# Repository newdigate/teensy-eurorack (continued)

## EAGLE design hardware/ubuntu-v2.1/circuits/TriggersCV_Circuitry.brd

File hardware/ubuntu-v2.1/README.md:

# ubuntu instrument v2.1
## [circuits](circuits)
## bom
 * teensy 3.6 board
 * blackaddr teensy guitaar audio pro shield

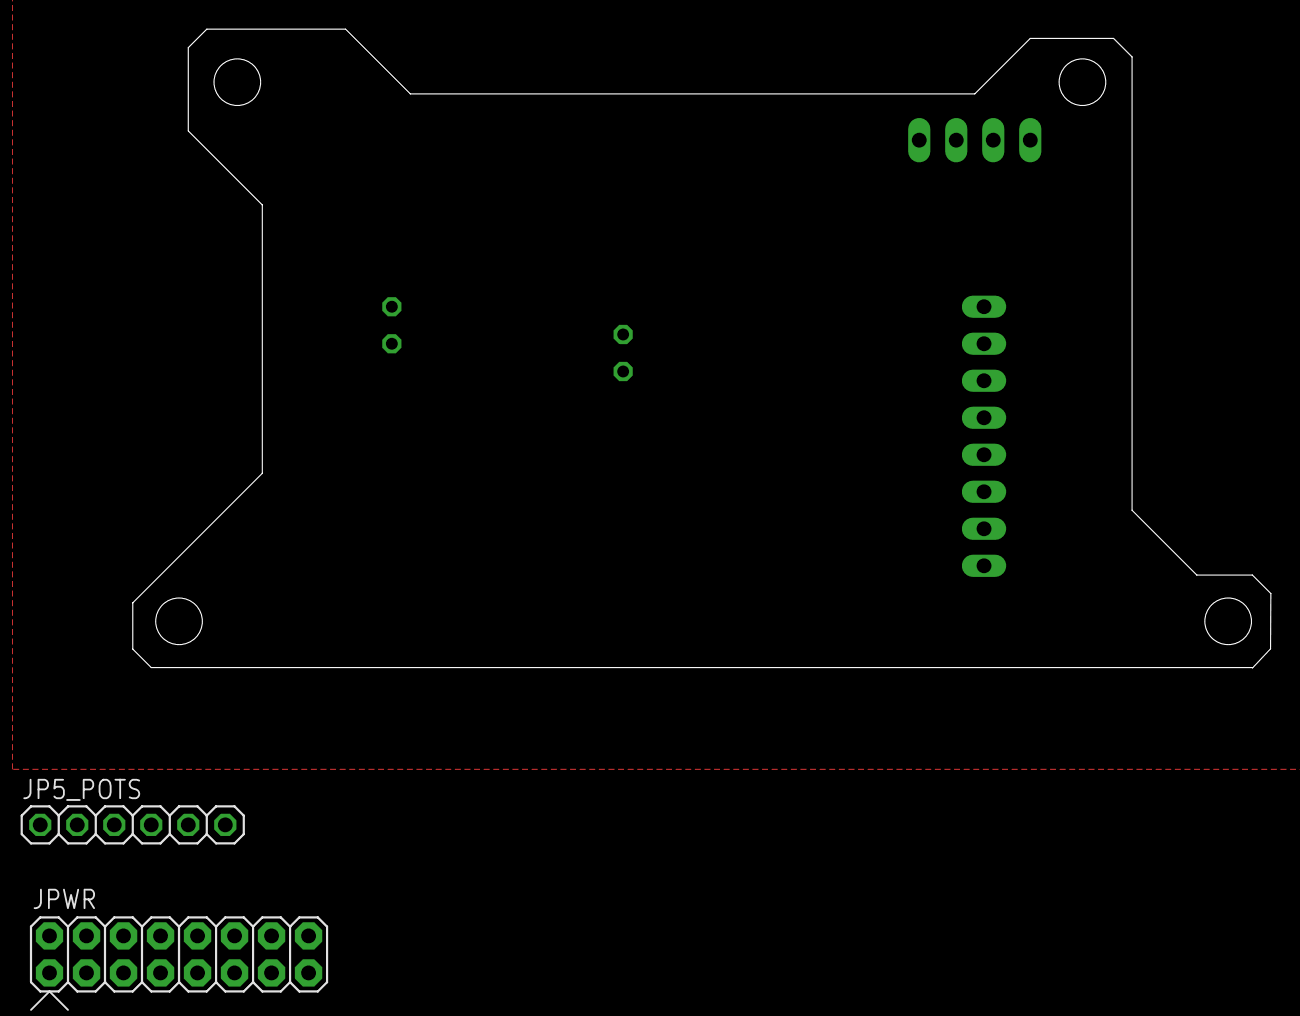
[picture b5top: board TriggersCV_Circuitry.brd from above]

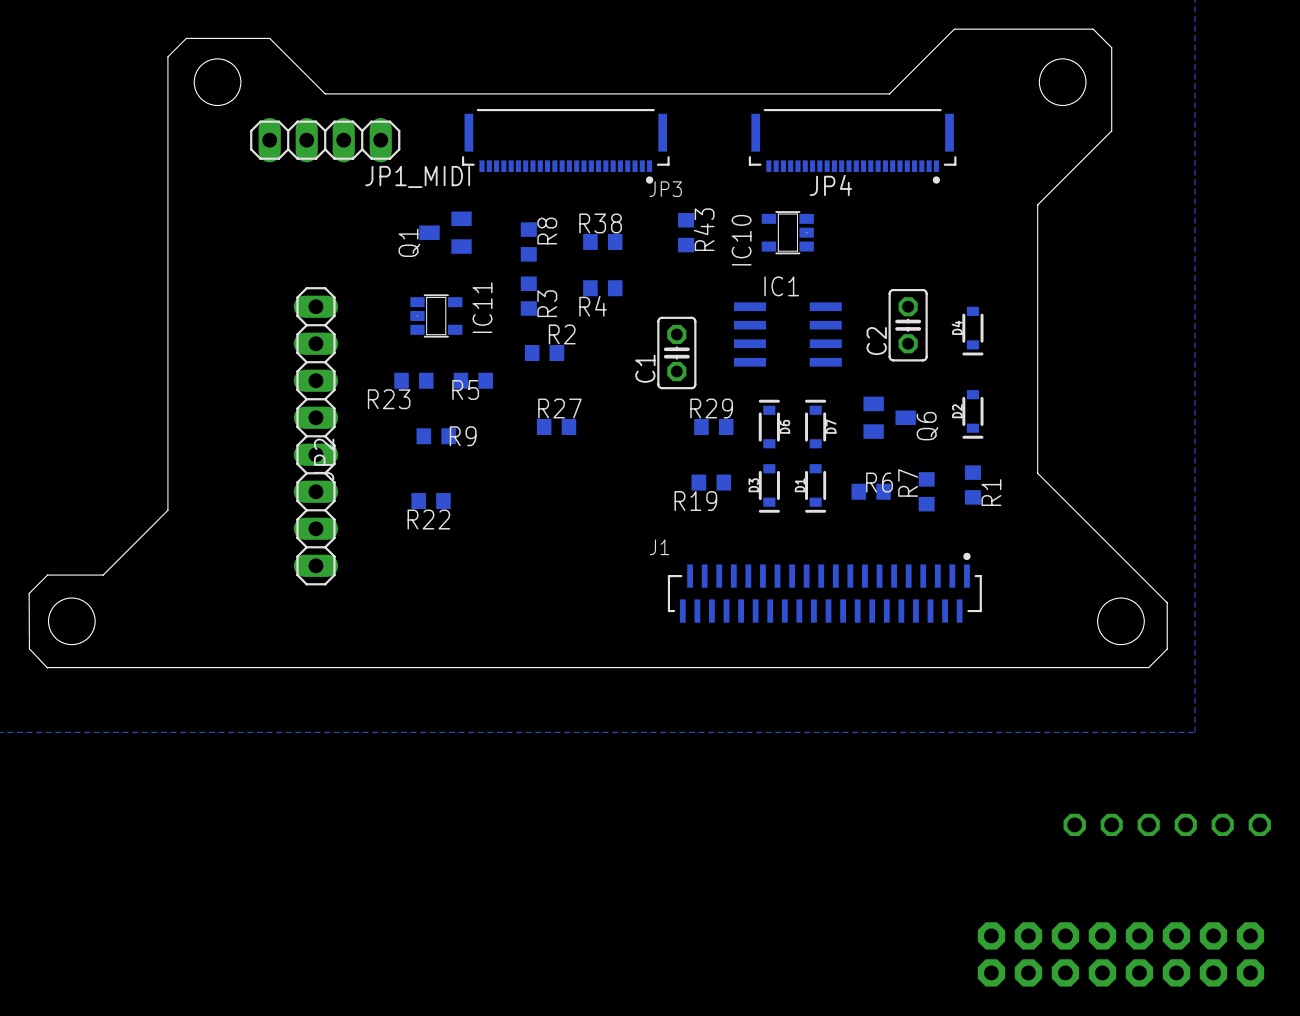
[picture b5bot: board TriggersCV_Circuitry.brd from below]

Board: 2 copper layers, 78.1 x 43.8 mm, 36 parts (34 on the bottom side), 49 nets, no tracks yet.

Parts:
C1, C2: 47p; C025-025X050
D1, D2, D3, D4, D6, D7: 250mA/100V; SPARKFUN-DISCRETESEMI_SOD-323
IC1: TL072D; SO08
IC10, IC11: 74AHCT1G125DBV; SOT23-5
J1: MOLEX_78127-1408MOLEX_78127-1408_0_0; MOLEX_78127-1408_0
JP1_MIDI: 1X04
JP2: 1X08
JP3, JP4: MOLEX_51281-2494MOLEX_51281-2494_0_0; MOLEX_51281-2494_0
JP5_POTS: PINHD-1X6; 1X06
JPWR: POWER; POWER_16
Q1, Q6: MMBT3904; SOT23-BEC
R1, R4, R7, R19: 1K; R0603
R2, R3, R5, R6: 100K; R0603
R8, R29: 100k; R0603
R9, R27: 10k; R0603
R22, R23: 47k; R0603
R38, R43: 1.0k; R0603

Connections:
+3V3: R9.2, R27.2
CV_IN_1: JP3.8, JP3.9
CV_IN_2: D1.A, D2.C, D3.A, D4.C, JP3.7, R1.1, R19.1
CV_OUT_1: JP3.10, JP3.11, R3.1, R4.1
CV_OUT_2: JP3.6, R6.1, R7.1
GND: D2.A, D4.A, D6.A, D7.A, IC1.4, IC10.1, IC10.3, IC11.1, IC11.3, J1.40, JP2.1, JP3.19, JP3.20, JP3.21, JP3.22, JP3.23, JP3.24, JP3.MP1, JP3.MP2, JP4.1, JP4.14, JP5_POTS.3, JP5_POTS.6, JPWR.3, JPWR.4, JPWR.5, JPWR.6, JPWR.7, JPWR.8, Q1.E, Q6.E, R22.1
MIDI_RX_PIN4: JP1_MIDI.1, JP3.12, JP3.13
MIDI_RX_PIN5: JP1_MIDI.2, JP3.14
MIDI_TX_PIN4: JP1_MIDI.3, JP3.15
MIDI_TX_PIN5: JP1_MIDI.4, JP3.16, JP3.17
unnamed: C1.1, IC1.2, R2.1, R3.2
unnamed: C2.1, IC1.6, R5.1, R6.2
unnamed: C1.2, IC1.1, R4.2
unnamed: C2.2, IC1.7, R7.2
unnamed: D7.C, Q1.B, R8.2
unnamed: IC10.4, R38.2
unnamed: IC11.4, R43.2
unnamed: D6.C, Q6.B, R29.2
SPI0_MOSI: J1.34, JP2.4
SPI0_SCLK: J1.37, JP2.3
T2_GATE_IN_A: J1.3, Q6.C, R27.1
T3_GATE_IN_B: J1.4, Q1.C, R9.1
T4_GATE_OUT_A: IC10.2, J1.5
T10_GATE_OUT_B: IC11.2, J1.6
T16_ENC1_A: J1.7, JP4.2
T24_ENC1_B: J1.8, JP4.3
T25_ENC1_SW: J1.9, JP4.4
T26_ENC2_A: J1.10, JP4.5
T27_ENC2_B: J1.11, JP4.6
T28_ENC2_SW: J1.12, JP4.7
T29_ENC3_A: J1.13, JP4.8
T30_ENC3_B: J1.14, JP4.9
T32_ENC3_SW: J1.15, JP4.10
TA14_POT_1: J1.16, JP5_POTS.2, R19.2
TA15_POT_2: J1.17, R1.2
TA17_ENC4_A: J1.19, JP4.11
TA18_ENC4_B: J1.20, JP4.12
TA19_ENC4_SW: J1.21, JP4.13
TDAC0: IC1.3, J1.23
TDAC1: IC1.5, J1.24
TFT_CS: J1.38, JP2.7
TFT_DC: J1.39, JP2.6
TFT_RST: J1.36, JP2.5
TRIG_IN_1: JP3.5, R29.1
TRIG_IN_2: JP3.3, R8.1
TRIG_OUT_1: JP3.4, R38.1
TRIG_OUT_2: JP3.1, JP3.2, R43.1
VCC: D1.C, D3.C, IC1.8, IC10.5, IC11.5, J1.33, JP2.2, JP2.8, JP5_POTS.1, JP5_POTS.4, JPWR.11, JPWR.12, R23.2
VCC/2: R2.2, R5.2, R22.2, R23.1

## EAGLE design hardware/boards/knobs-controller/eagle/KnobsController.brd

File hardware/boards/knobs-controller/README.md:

# Knobs Controller

```
status:
   01 Sept 2019: pcb delivery failure, pcbs re-ordered
   13 Dec 2019: 
     * v1.6: issue with tx/rx connection to mainboard fixed
```
## credits
* this board is based on [Arduino MKR Zero](https://store.arduino.cc/arduino-mkr-zero-i2s-bus-sd-for-sound-music-digital-audio-data) design by Arturo Guadalupi (v5.0)

## build
* build details for knob controller can be found here - [BUILD.md](BUILD.md) 
* BOM can be found here [Bill-of-materials.md](Bill-of-materials.md)

## quick details
An independent rotary encoder and potentiometer breakout board based on Arduino MKR Zero
* SAMD21G18A-MU 32bit micro-controller @ 48 MHz. 
* 4 x 12bit rotary potentiometers
* 3 x RGB Illuminated rotary encoder w/ switch
* Communicates with main-board via serial rx / tx

## objectives
Introducing an intermediate micro-controller (ARM cortex M0 / SAMD21G) 
* reduces complexity of mainboard
* reduces number of anlog and digital pins required by teensy for haptic input (knobs and pots)
* simplyfies and unifies mainboard firmware for 

some firmware will run on the M0 microcontroller to relay input (knob value changes) back to the mainboard and receive commands (eg. to light up RGB rotaries ) via serial TX / RX, 

Number of signal required between main-board and knobs controller is reduced to: +5V, GND, TX, RX; 
## revisions
* v1.5: board size reduced slightly on the right hand side to allow assembly to fit in to a 6U high rack mount unit.
* v1.6: 
  * fixed tx/rx connection
  * moved connector to mainboard out of the way

## todo 
- [ ] change mcu to ATSAMD21G18A-AU (jlc pcb assembly friendly)

## How did this happen?
I want to upgrade the mainboard to using a teensy 4.0 and I don't want to rely on using the pins on the underside of the teensy. 

I started with the schematic of [arduino mkr zero](https://create.arduino.cc/projecthub/products/arduino-mkr-zero) (available from arduino -- [MKRZero-reference.zip](https://content.arduino.cc/assets/MKRZero-reference.zip) as eagle .sch and .brd) and removed components from the circuit which I don't need. I needed to keep the SWD (Serial wire debug) pins on the micro-controller available, so I can upload a bootloader- as the usb connection won't be available until the bootloader is programmed via the 6-pin SWD header.

## Images

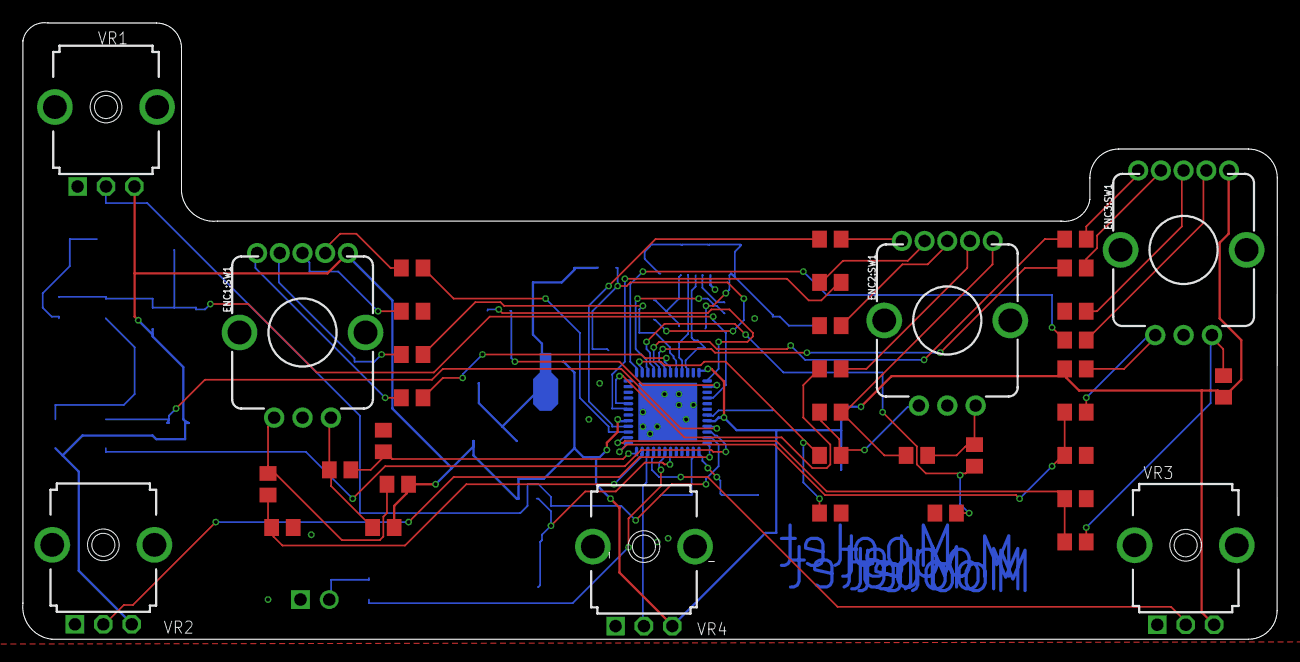
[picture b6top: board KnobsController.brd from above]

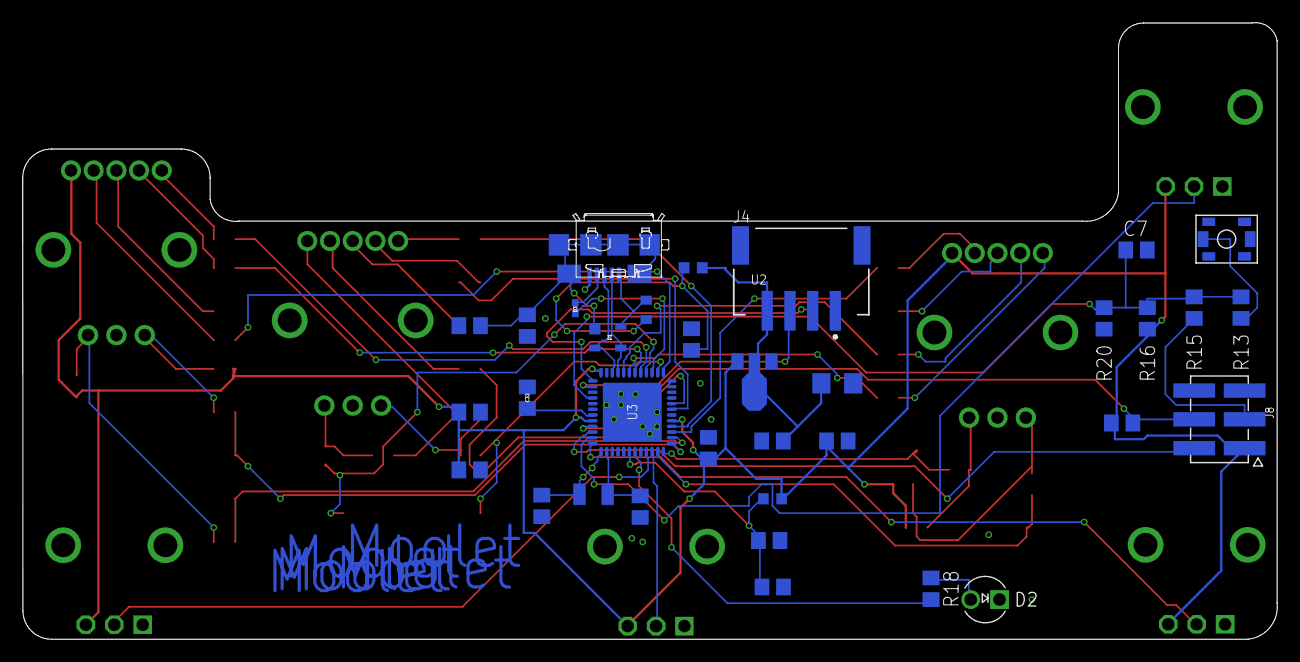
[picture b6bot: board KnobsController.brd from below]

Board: 2 copper layers, 110.5 x 54.3 mm, 71 parts (34 on the bottom side), 61 nets.

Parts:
C4: 1nF; RESISTOR-NICK_C0805
C5: 1nF; RESISTOR-NICK_C1206
C6: 4.7nF; RESISTOR-NICK_C0805
C7: 100nF; C0805
C8, C10, C32: 1uF; RESISTOR-NICK_C0805
C9, C11: 20pF; RESISTOR-NICK_C0805
C19, C28, C29, C30: 100nF; RESISTOR-NICK_C0805
C27: 4.7uF; RESISTOR-NICK_C0805
D1: MK1_ZERO_PRTR5V0U2X,215; MK1_ZERO_SOT190P230X110-4N
D2: LED_LTL-1CHG; LED_RADIAL_3MM
D3: MK1_ZERO_PMEG2005EL; MK1_ZERO_SODFL1008X40N-882D
ENC1:C1, ENC1:C3, ENC2:C1, ENC2:C3, ENC3:C1, ENC3:C3: 10nF; C0805
ENC1:R1, ENC1:R4, ENC1:R5, ENC1:R7, ENC1:R9, ENC2:R1, ENC2:R4, ENC2:R5, ENC2:R7, ENC2:R9, ENC3:R1, ENC3:R4, ENC3:R5, ENC3:R7, ENC3:R9: 10k; R0805
ENC1:R12, ENC1:R13, ENC1:R14, ENC2:R12, ENC2:R13, ENC2:R14, ENC3:R12, ENC3:R13, ENC3:R14: 10; R0805
ENC1:SW1, ENC2:SW1, ENC3:SW1: Rotary Encoder; ENCODER_LED_3_KIT
F2: MK1_ZERO_MF-FSMF050X-2; MK1_ZERO_0603-F1608X100N
J1: ZX62-AB-5PA(31); MK1_ZERO_USBMICRO-ZX62-AB-5PA
J4: JST---S4B-PH-SM4-TB(LF)(SN)_JST_S4B-PH-SM4-TB_LF_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; JST---S4B-PH-SM4-TB(LF)(SN)_JST_S4B-PH-SM4-TB_LF_SN_0
J8: 2X3_SMT
L2, L6: MK1_ZERO_BLM18PG471SN1D; MK1_ZERO_0603-1608X90N
R2: 1M; RESISTOR-NICK_R0805
R7: 1K; R0805
R13, R20: 330R; R0805
R15: 39R; R0805
R16: 10K; R0805
R18: 330R; RESISTOR-NICK_R0805
U2: MK1_ZERO_AP7215-33YG-13; MK1_ZERO_SOT150P400X160-3N
U3: MK1_ZERO_ATSAMD21G18A-48; MK1_ZERO_QFN50P700X700X90-49XN-EPSQ515
U$9: PUSHBUTTON2; C&K_PTS820_NOPEGS
VR1, VR2, VR3, VR4: MUSICTHINGMODULAR_9MM_SNAP-IN_POT
Y1: 32.768KHz; MK1_ZERO_QUARZO-ABS07

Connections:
+3V3: C10.1, C19.1, C28.1, C29.1, ENC1:R4.2, ENC1:R7.1, ENC1:SW1.5, ENC3:R4.2, ENC3:R7.1, ENC3:SW1.5, J8.1, L6.1, R7.2, R16.2, U2.3, U3.17, U3.36, U3.44, VR1.3, VR2.3, VR3.3, VR4.3
ENC1:A: ENC1:R4.1, ENC1:R5.1, ENC1:SW1.A
ENC1:B: ENC1:R7.2, ENC1:R9.2, ENC1:SW1.B
ENC1:BLUE_RAW: ENC1:R14.1, ENC1:SW1.4
ENC1:GREEN_RAW: ENC1:R13.1, ENC1:SW1.2
ENC1:RED_RAW: ENC1:R12.1, ENC1:SW1.1
ENC1:SWITCH: ENC1:R1.2, ENC1:SW1.3
ENC2:3.3V: ENC2:R4.2, ENC2:R7.1, ENC2:SW1.5
ENC2:A: ENC2:R4.1, ENC2:R5.1, ENC2:SW1.A
ENC2:B: ENC2:R7.2, ENC2:R9.2, ENC2:SW1.B
ENC2:BLUE_RAW: ENC2:R14.1, ENC2:SW1.4
ENC2:GREEN_RAW: ENC2:R13.1, ENC2:SW1.2
ENC2:RED_RAW: ENC2:R12.1, ENC2:SW1.1
ENC2:SWITCH: ENC2:R1.2, ENC2:SW1.3
ENC3:A: ENC3:R4.1, ENC3:R5.1, ENC3:SW1.A
ENC3:B: ENC3:R7.2, ENC3:R9.2, ENC3:SW1.B
ENC3:BLUE_RAW: ENC3:R14.1, ENC3:SW1.4
ENC3:GREEN_RAW: ENC3:R13.1, ENC3:SW1.2
ENC3:RED_RAW: ENC3:R12.1, ENC3:SW1.1
ENC3:SWITCH: ENC3:R1.2, ENC3:SW1.3
GND: C4.2, C5.2, C6.2, C7.2, C8.2, C9.1, C10.2, C11.1, C19.2, C27.2, C28.2, C29.2, C30.2, C32.2, D2.C, ENC1:C1.2, ENC1:C3.2, ENC1:R1.1, ENC1:SW1.C, ENC2:C1.2, ENC2:C3.2, ENC2:R1.1, ENC2:SW1.C, ENC3:C1.2, ENC3:C3.2, ENC3:R1.1, ENC3:SW1.C, J1.5, J4.1, J8.5, R2.1, U2.1, U3.5, U3.18, U3.35, U3.42, U3.49, U$9.1, U$9.2, U$9.3, U$9.4, U$9.5, VR1.1, VR2.1, VR3.1, VR4.1
N17650912: D1.4, F2.2, J1.1
N17658775: R13.1, U$9.6
N17852357: C27.1, C30.1, L6.2, U3.6
N17852431: C32.1, U3.43
unnamed: C6.1, D1.1, J1.6, J1.7, J1.8, J1.9, J1.10, J1.11, R2.2
unnamed: C4.1, F2.1, L2.1
unnamed: J8.3, R15.1
unnamed: D2.A, R18.2
PA00_XIN32: C11.2, U3.1, Y1.2
PA01_XOUT32: C9.2, U3.2, Y1.1
PA04_AIN4: U3.9, VR3.2
PA05_AIN5: U3.10, VR4.2
PA06_AIN6: ENC1:C3.1, ENC1:R5.2, U3.11
PA07_AIN7: ENC1:C1.1, ENC1:R9.1, U3.12
PA08_S0_I2C_SDA: ENC3:C3.1, ENC3:R5.2, U3.13
PA09_S0_I2C_SCL: ENC3:C1.1, ENC3:R9.1, U3.14
PA10_TCC0-W2: ENC1:R14.2, U3.15
PA11_TCC0-W3: ENC2:R12.2, U3.16
PA16_S1_MOSI: ENC3:R14.2, U3.25
PA17_S1_SCK: ENC2:C3.1, ENC2:R5.2, U3.26
PA18_USB_ID: D3.A, U3.27
PA19_S1_MISO: ENC2:C1.1, ENC2:R9.1, U3.28
PA20_TCC0-W6: ENC3:R12.2, U3.29
PA21_TCC0-W7: ENC3:R13.2, U3.30
PA22_TC4-W0: ENC1:R12.2, U3.31
PA23_TC4-W1: ENC1:R13.2, U3.32
PA30_SWCLK: J8.4, R7.1, U3.45
PA31_SWDIO: J8.2, U3.46
PB02_AIN10: U3.47, VR1.2
PB03_AIN11: U3.48, VR2.2
PB08_LED: R18.1, U3.7
PB10_TCC0-W4: ENC2:R13.2, U3.19
PB11_TCC0-W5: ENC2:R14.2, U3.20
PB22_S5_TX: J4.2, U3.37
PB23_S5_RX: J4.3, U3.38
RESETN: C7.1, R13.2, R15.2, R16.1, R20.1, U3.40
USB_ID: D3.C, J1.4
USB_N: D1.3, J1.2, U3.33
USB_P: D1.2, J1.3, U3.34
VUSB: C5.1, C8.1, J4.4, L2.2, U2.2

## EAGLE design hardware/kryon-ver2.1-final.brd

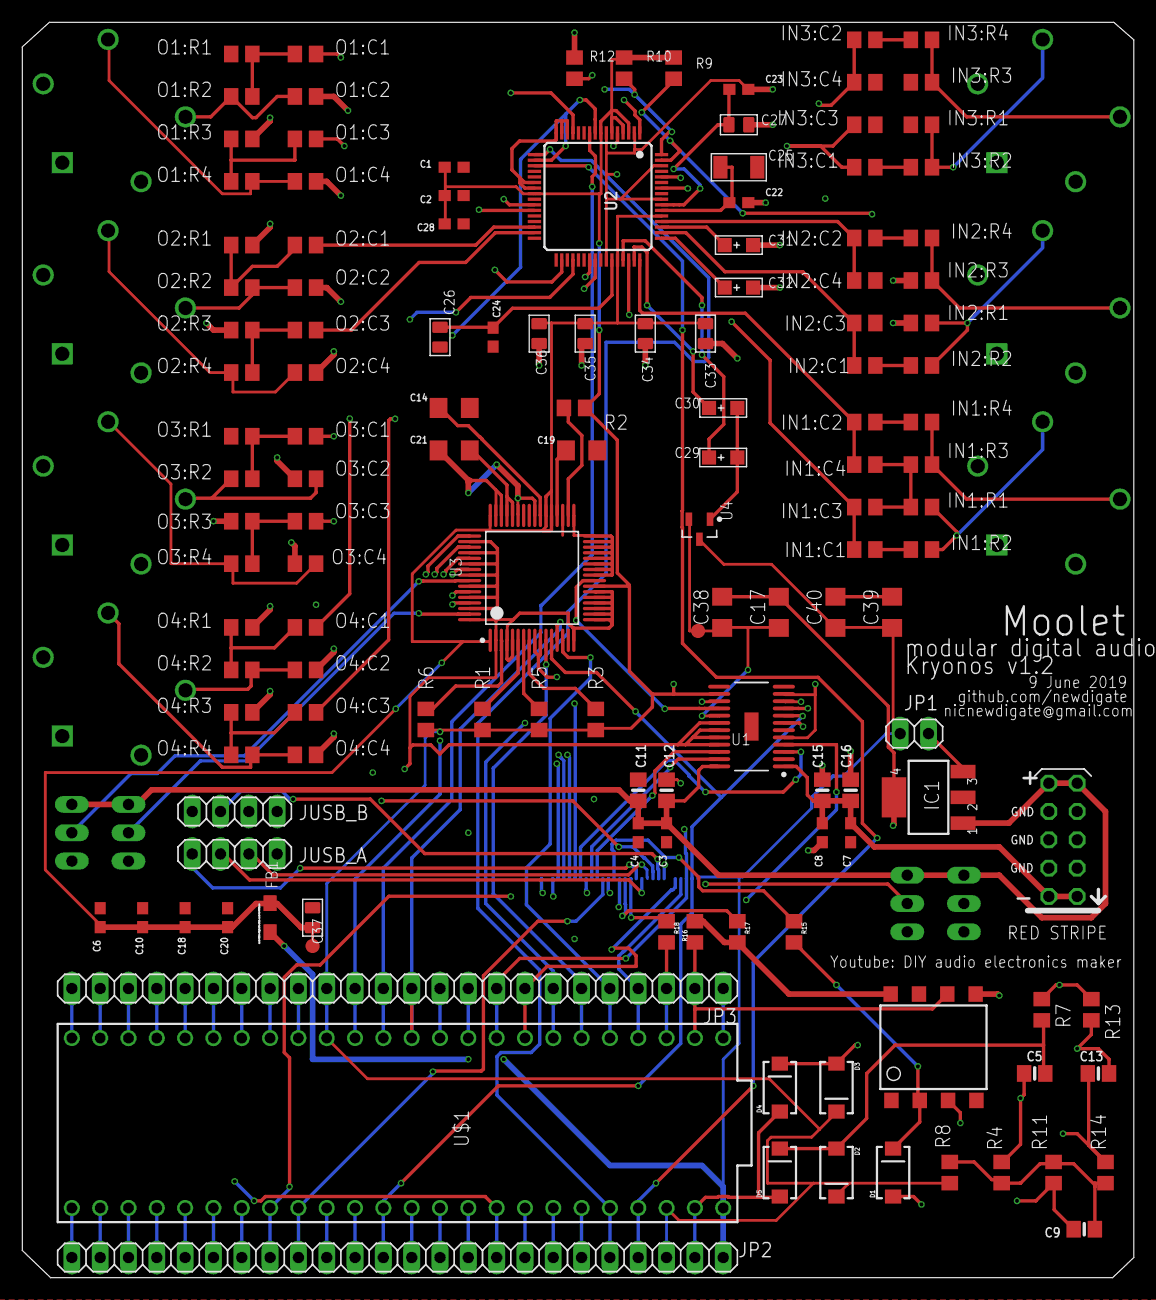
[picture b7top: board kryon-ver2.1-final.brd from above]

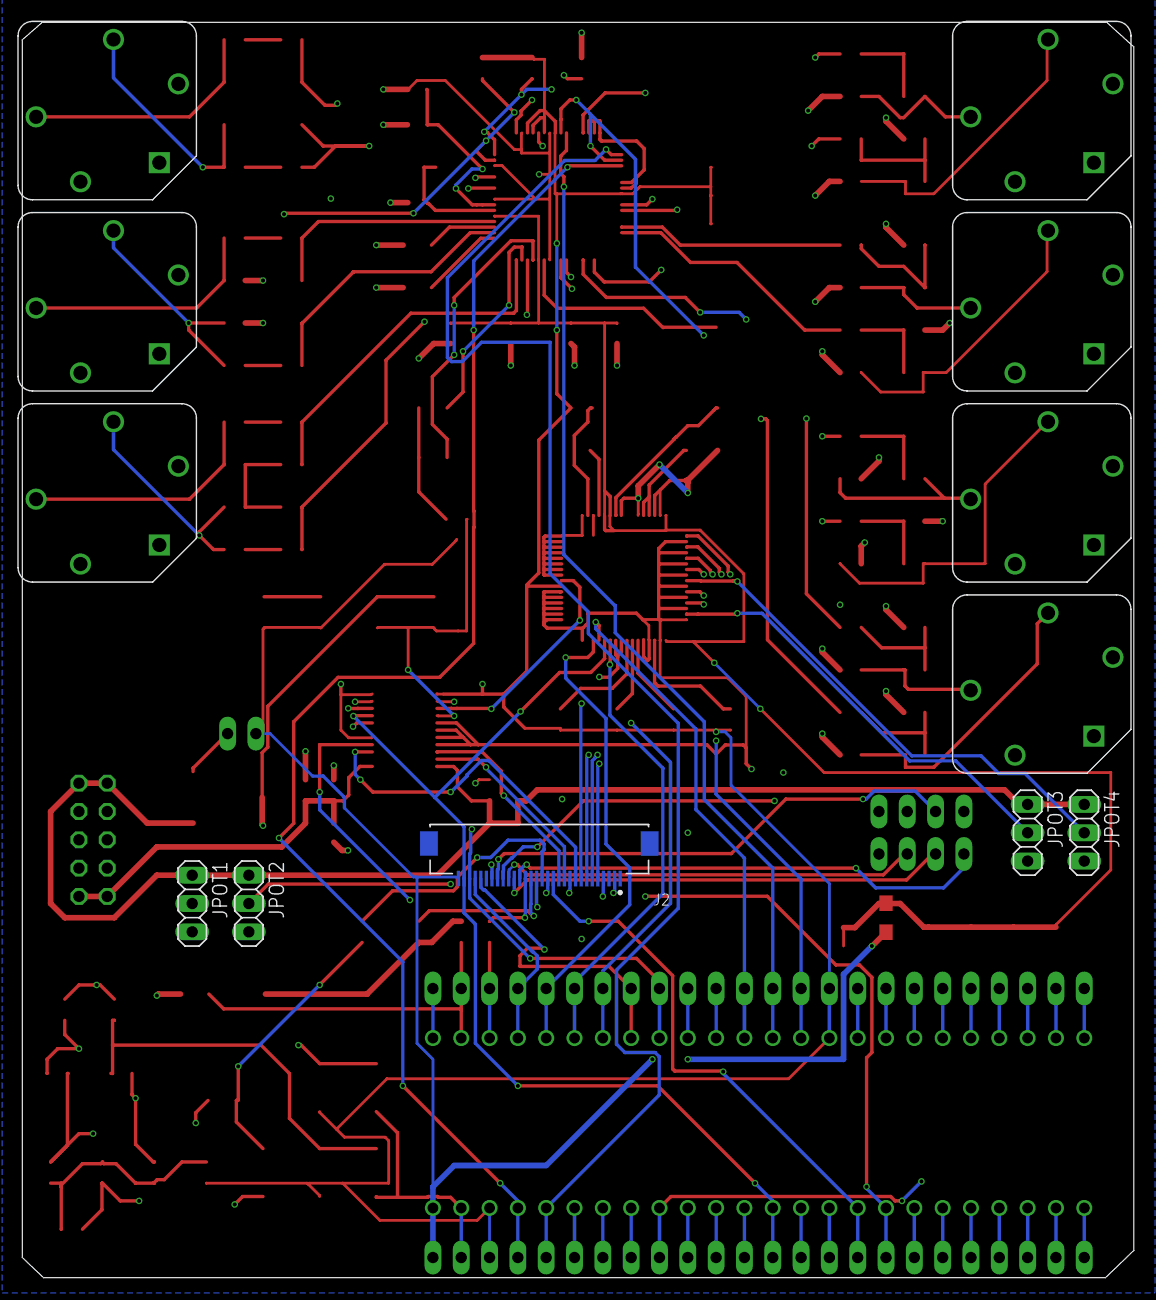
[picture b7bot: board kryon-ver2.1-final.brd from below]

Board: 4 copper layers, 99.7 x 112.6 mm, 147 parts (12 on the bottom side), 136 nets.

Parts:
C1, C2, C3, C4, C6, C7, C8, C10, C18, C20, C22, C23, C24, C28: 0.1uF; 0603
C5, C9, C11, C12, C13, C15, C16: 10uF; 0805-NO
C14, C19: 1.0uF; 1206
C17, C38, C39, C40: 0.1uF; C1206
C21: 10uF; 1206
C25: 100uf; C1206
C26: 4.7uf; C0805
C27: 22uf; C0805
C29, C30, C31, C32: 4.7uf; AVX-A
C33: 10uf; C0805
C34, C35: 100nf; C0805
C36, C37: 10nf; C0805
D1, D2, D3, D4, D5: SMA-DIODE
FB1: MURATA_BLM21PG221SN1DMURATA_BLM21PG221SN1D_0_1; MURATA_BLM21PG221SN1D_1
IC1: LM340MP-05; SOT223
IN1:C1, IN1:C2, IN2:C1, IN2:C2, IN3:C1, IN3:C2: 10uF; C0805
IN1:C3, IN1:C4, IN2:C3, IN2:C4, IN3:C3, IN3:C4: 2700pF; C0805
IN1:R1, IN1:R3, IN2:R1, IN2:R3, IN3:R1, IN3:R3: 100K; R0805
IN1:R2, IN1:R4, IN2:R2, IN2:R4, IN3:R2, IN3:R4: 150; R0805
IN1:U$3, IN2:U$3, IN3:U$3: ACJS-MV-5; ACJS-MV5
J2: MOLEX_52892-3033MOLEX_52892-3033_0_0; MOLEX_52892-3033_0
JP1: 1X02
JP2, JP3: 1X24
JPOT1, JPOT2, JPOT3, JPOT4: 1X03
JUSB_A: 1X04
JUSB_B: 1X04
O1:C1, O1:C3, O2:C1, O2:C3, O3:C1, O3:C3, O4:C1, O4:C3: 4.7uF; C0805
O1:C2, O1:C4, O2:C2, O2:C4, O3:C2, O3:C4, O4:C2, O4:C4: 2700pF; C0805
O1:J_OUT, O2:J_OUT, O3:J_OUT, O4:J_OUT: ACJS-MV-5; ACJS-MV5
O1:R1, O1:R3, O2:R1, O2:R3, O3:R1, O3:R3, O4:R1, O4:R3: 10K; R0805
O1:R2, O1:R4, O2:R2, O2:R4, O3:R2, O3:R4, O4:R2, O4:R4: 560; R0805
R1, R2, R3, R5, R6: 4.7k; R0805
R4, R7, R13, R14: 47k; R0805
R8: 10k; R0805
R9, R10, R12: 2K; R0805
R11: 2.2k; R0805
R15, R16, R17, R18: 220; R0805
SV1: EURO_POWER_HEADERREGULAR; EURO_POWER_HEADER
TP1, TP2: TEST-POINT3X5; PAD.03X.05
U1: ANALOG_DEVICES_AD5754BREZANALOG_DEVICES_AD5754BRE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; ANALOG_DEVICES_AD5754BREZ_2
U2: CS42448; LQFP64L
U3: ANALOG_DEVICES_AD7606BSTZANALOG_DEVICES_AD7606BST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; ANALOG_DEVICES_AD7606BSTZ_2
U4: MICROCHIP_MCP1700T-2502E-TTMICROCHIP_MCP1700T-250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; MICROCHIP_MCP1700T-2502E-TT_0
U$1: TEENSY_3.6_DIL
U$2: OPTO_DARL_6N138S; 8-SMD

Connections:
3V3: C1.1, C2.1, C28.2, D2.C, D3.C, JP2.3, JP3.15, R1.1, R2.2, R3.1, R5.2, R6.1, R8.2, R9.1, R10.1, U1.5, U1.11, U1.14, U2.3, U2.4, U2.6, U2.8, U2.24, U3.23, U$1.3.3V, U$1.3.3V3
56: D1.C, R15.2, U$2.2
ADC_DATA: JP2.14, U2.13, U$1.13
AD_BUSY: JP3.5, U3.14, U$1.3
AD_BYTE_SELECT: R1.2, U3.6
AD_CONVST: JP3.7, U3.9, U3.10, U$1.5
AD_CS: JP3.12, U3.13, U$1.10
AD_OS0: R6.2, U3.3
AD_RANGE: R3.2, U3.8
AD_REFCAP_A: C21.1, U3.44, U3.45
AD_REFSEL: R2.1, U3.34
AD_REGCAP1: C19.1, U3.36
AD_REGCAP2: C14.1, U3.39
AD_RESET: JP3.6, U3.11, U$1.4
AD_STBY: R5.1, U3.7
AD_V1: J2.5, U3.49
AD_V2: J2.6, U3.51
AD_V3: J2.7, U3.53
AD_V4: J2.8, U3.55
AD_V5: JPOT4.2, U3.57
AD_V6: JPOT1.2, U3.59
AD_V7: JPOT2.2, U3.61
AD_V8: JPOT3.2, U3.63
AVDD: C3.1, C4.1, C11.1, C12.1, IC1.1, JPOT1.1, JPOT2.1, JPOT3.1, JPOT4.1, SV1.9, SV1.10, U1.24
AVIN: C6.1, C10.1, C18.1, C20.1, C33.2, C34.2, C35.2, C36.2, C37.2, FB1.2, TP2.P$1, U2.44, U2.53, U3.1, U3.37, U3.38, U3.48
AVSS: C7.1, C8.1, C15.1, C16.1, SV1.1, SV1.2, U1.1
BCLK: JP3.11, U2.9, U2.18, U$1.9
DAC_DATA: JP2.5, U2.17, U$1.22/A8
DA_SYNC: JP2.12, U1.7, U$1.15/A1
DA_V1: J2.9, U1.3
DA_V2: J2.10, U1.4
DA_V3: J2.11, U1.23
DA_V4: J2.12, U1.22
DA_V5: J2.13, JP2.16, U$1.A22
DA_V6: J2.14, JP2.17, U$1.A21
GND: C1.2, C2.2, C3.2, C4.2, C6.2, C7.2, C8.2, C10.2, C11.2, C12.2, C14.2, C15.2, C16.2, C17.2, C18.2, C19.2, C20.2, C21.2, C22.2, C23.2, C24.2, C25.1, C26.1, C27.1, C28.1, C29.-, C30.-, C31.-, C32.-, C33.1, C34.1, C35.1, C36.1, C37.1, C38.2, C39.2, C40.2, IC1.4, IN1:C3.2, IN1:C4.2, IN1:R1.1, IN1:R3.1, IN1:U$3.P$1, IN1:U$3.P$2, IN1:U$3.P$5, IN2:C3.2, IN2:C4.2, IN2:R1.1, IN2:R3.1, IN2:U$3.P$1, IN2:U$3.P$2, IN2:U$3.P$5, IN3:C3.2, IN3:C4.2, IN3:R1.1, IN3:R3.1, IN3:U$3.P$1, IN3:U$3.P$2, IN3:U$3.P$5, J2.1, JP2.15, JP3.1, JPOT1.3, JPOT2.3, JPOT3.3, JPOT4.3, JUSB_A.4, JUSB_B.4, O1:C2.2, O1:C4.2, O1:J_OUT.P$1, O1:J_OUT.P$2, O1:J_OUT.P$5, O1:R1.1, O1:R3.1, O2:C2.2, O2:C4.2, O2:J_OUT.P$1, O2:J_OUT.P$2, O2:J_OUT.P$5, O2:R1.1, O2:R3.1, O3:C2.2, O3:C4.2, O3:J_OUT.P$1, O3:J_OUT.P$2, O3:J_OUT.P$5, O3:R1.1, O3:R3.1, O4:C2.2, O4:C4.2, O4:J_OUT.P$1, O4:J_OUT.P$2, O4:J_OUT.P$5, O4:R1.1, O4:R3.1, R12.1, SV1.3, SV1.4, SV1.5, SV1.6, SV1.7, SV1.8, U1.10, U1.15, U1.18, U1.19, U1.20, U1.21, U2.2, U2.7, U2.14, U2.15, U2.16, U2.22, U2.23, U2.42, U2.56, U2.62, U3.2, U3.4, U3.5, U3.16, U3.17, U3.18, U3.19, U3.20, U3.21, U3.22, U3.25, U3.26, U3.27, U3.28, U3.29, U3.30, U3.31, U3.32, U3.33, U3.35, U3.40, U3.41, U3.43, U3.46, U3.47, U3.50, U3.52, U3.54, U3.56, U3.58, U3.60, U3.62, U3.64, U4.1, U$1.GND, U$1.GND1, U$2.5
IN1:N$1: IN1:R1.2, IN1:R2.1, IN1:U$3.P$4
IN1:N$7: IN1:C1.2, IN1:R2.2
IN1:N$10: IN1:R3.2, IN1:R4.1, IN1:U$3.P$3
IN1:N$11: IN1:C2.2, IN1:R4.2
IN2:N$1: IN2:R1.2, IN2:R2.1, IN2:U$3.P$4
IN2:N$7: IN2:C1.2, IN2:R2.2
IN2:N$10: IN2:R3.2, IN2:R4.1, IN2:U$3.P$3
IN2:N$11: IN2:C2.2, IN2:R4.2
IN3:N$1: IN3:R1.2, IN3:R2.1, IN3:U$3.P$4
IN3:N$7: IN3:C1.2, IN3:R2.2
IN3:N$10: IN3:R3.2, IN3:R4.1, IN3:U$3.P$3
IN3:N$11: IN3:C2.2, IN3:R4.2
LRCLK: JP2.4, U2.5, U2.19, U$1.23/A9
MCLK: JP3.13, U2.10, U$1.11
MIDI_IN_PIN4: D1.A, J2.16, U$2.3
MIDI_IN_PIN5: J2.15, R15.1
MIDI_OUT_PIN4: J2.18, R18.1
MIDI_OUT_PIN5: J2.17, R17.1
unnamed: IC1.3, JP1.1
unnamed: JP3.10, U$1.8
unnamed: JP2.7, U$1.20/A6
unnamed: C22.1, C25.2, U2.54
unnamed: C23.1, C27.2, U2.55
unnamed: C24.1, C26.2, U2.43
unnamed: C29.+, U2.45
unnamed: C30.+, U2.47
unnamed: IN1:C1.1, IN1:C3.1, U2.46
unnamed: IN1:C2.1, IN1:C4.1, U2.48
unnamed: IN3:C1.1, IN3:C3.1, U2.58
unnamed: IN2:C2.1, IN2:C4.1, U2.52
unnamed: IN2:C1.1, IN2:C3.1, U2.50
unnamed: C31.+, U2.51
unnamed: O1:C1.2, U2.26
unnamed: O1:C3.1, U2.27
unnamed: O2:C1.2, U2.30
unnamed: C32.+, U2.49
unnamed: O2:C3.1, U2.31
unnamed: O3:C1.2, U2.34
unnamed: O3:C3.1, U2.36
unnamed: O4:C1.2, U2.39
unnamed: O4:C3.1, U2.40
unnamed: R12.2, U2.1
unnamed: JP2.6, U$1.21/A7
unnamed: JP3.16, U$1.24
unnamed: JP3.17, U$1.25
unnamed: IN3:C2.1, IN3:C4.1, U2.60
unnamed: JP3.18, U$1.26
unnamed: JP3.19, U$1.27
unnamed: JP3.20, U$1.28
unnamed: JP3.21, U$1.29
unnamed: JP3.22, U$1.30
unnamed: JP3.23, U$1.31/A12
unnamed: JP3.24, U$1.32/A13
unnamed: JP2.18, U$1.39/A20
unnamed: JP2.19, U$1.38/A19
unnamed: JP2.20, U$1.37/A18
unnamed: JP2.22, U$1.35/A16
unnamed: JP2.21, U$1.36/A17
unnamed: JP2.23, U$1.34/A15
unnamed: JP2.24, U$1.33/A14
O1:N$1: O1:C3.2, O1:R3.2, O1:R4.1
O1:N$3: O1:C2.1, O1:J_OUT.P$3, O1:R2.2
O1:N$4: O1:C4.1, O1:J_OUT.P$4, O1:R4.2
O1:N$17: O1:C1.1, O1:R1.2, O1:R2.1
O2:N$1: O2:C3.2, O2:R3.2, O2:R4.1
O2:N$3: O2:C2.1, O2:J_OUT.P$3, O2:R2.2
O2:N$4: O2:C4.1, O2:J_OUT.P$4, O2:R4.2
O2:N$17: O2:C1.1, O2:R1.2, O2:R2.1
O3:N$1: O3:C3.2, O3:R3.2, O3:R4.1
O3:N$3: O3:C2.1, O3:J_OUT.P$3, O3:R2.2
O3:N$4: O3:C4.1, O3:J_OUT.P$4, O3:R4.2
O3:N$17: O3:C1.1, O3:R1.2, O3:R2.1
O4:N$1: O4:C3.2, O4:R3.2, O4:R4.1
O4:N$3: O4:C2.1, O4:J_OUT.P$3, O4:R2.2
O4:N$4: O4:C4.1, O4:J_OUT.P$4, O4:R4.2
O4:N$17: O4:C1.1, O4:R1.2, O4:R2.1
RX: JP3.2, R16.1, U$1.0, U$2.6
SCL: JP2.8, R9.2, U2.63, U$1.19/A5
SDA: JP2.9, R10.2, U2.64, U$1.18/A4
SPI0_MISO: JP3.14, U1.16, U3.24, U$1.12
SPI0_MOSI: J2.28, JP3.9, U1.9, U$1.7
SPI0_SCK: J2.29, JP2.13, U1.8, U3.12, U$1.14/A0
T16_A2: C5.1, JP2.11, R4.2, U$1.16/A2
T17_A3: C13.1, JP2.10, R14.2, U$1.17/A3
TAGND: C9.2, D4.A, D5.A, J2.2, JP2.2, R7.1, R11.1, R13.1, U$1.AGND
TEENSY_AD_OFFSET: C9.1, R4.1, R8.1, R11.2, R14.1
TFT_CS: J2.26, JP3.8, U$1.6
TFT_DC: J2.27, JP3.4, U$1.2
TX: JP3.3, R18.2, U$1.1
T_ANALOG_LEFT: C5.2, D2.A, D5.C, R7.2
T_ANALOG_RIGHT: C13.2, D3.A, D4.C, J2.4, R13.2
USB_A_D+: J2.21, JUSB_A.3
USB_A_D-: J2.20, JUSB_A.2
USB_A_VCC: J2.19, JUSB_A.1
USB_B_D+: J2.24, JUSB_B.3
USB_B_D-: J2.23, JUSB_B.2
USB_B_VCC: J2.22, JUSB_B.1
VCC: R16.2, R17.2, U$2.8
VIN: C39.1, C40.1, FB1.1, J2.30, JP1.2, JP2.1, U4.3, U$1.VIN
VREF: C17.1, C38.1, TP1.P$1, U1.17, U4.2

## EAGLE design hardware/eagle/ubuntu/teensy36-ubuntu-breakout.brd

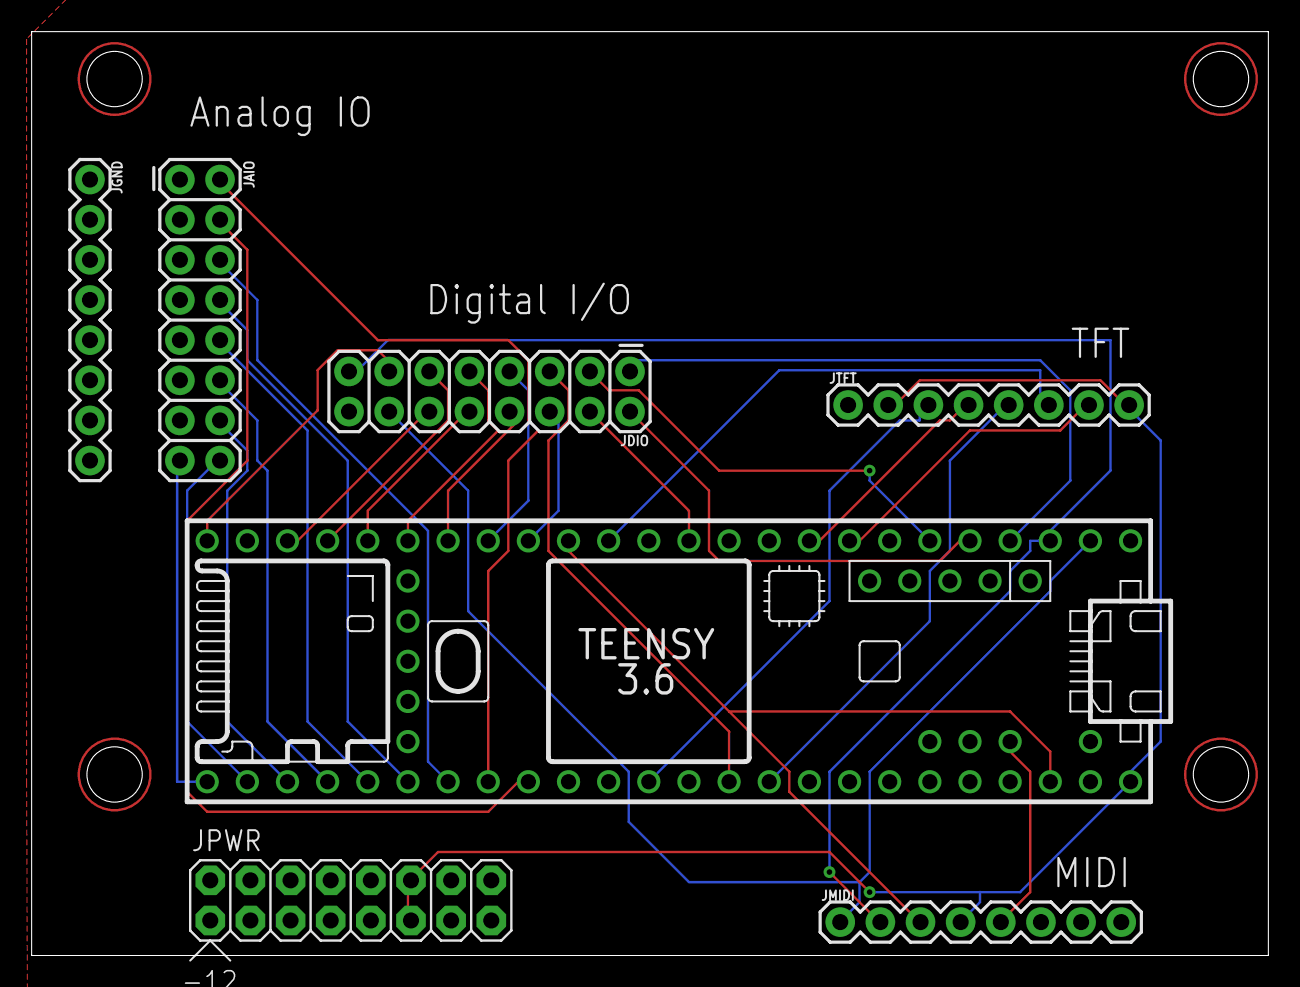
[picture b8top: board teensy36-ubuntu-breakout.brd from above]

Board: 2 copper layers, 78.2 x 58.5 mm, 7 parts (0 on the bottom side), 33 nets.

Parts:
JAIO: 2X8
JDIO: 2X8
JGND: 1X08
JMIDI: 1X08
JPWR: POWER; POWER_16
JTFT: 1X08
U$3: TEENSY_3.5/3.6

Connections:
3V3: JMIDI.3, U$3.3V3, U$3.3V3_LO
AREF: JMIDI.5, U$3.AREF
GND: JAIO.1, JAIO.3, JAIO.5, JAIO.7, JAIO.9, JAIO.11, JAIO.13, JDIO.16, JGND.1, JGND.2, JGND.3, JGND.4, JGND.5, JGND.6, JGND.7, JGND.8, JMIDI.6, JMIDI.7, JMIDI.8, JPWR.3, JPWR.4, JPWR.5, JPWR.6, JPWR.7, JPWR.8, JTFT.1, U$3.GND, U$3.GND2
MIDI_RX: JDIO.14, JMIDI.1, U$3.0/RX
MIDI_TX: JDIO.15, JMIDI.2, U$3.1/TX
SPI0_MOSI: JTFT.4, U$3.7
SPI0_SCLK: JTFT.3, U$3.14/A0
T2: JDIO.1, U$3.2
T3: JDIO.2, U$3.3/CANTX
T4: JDIO.3, U$3.4/CANRX
T10: JDIO.4, U$3.10/CS
T16: JDIO.5, U$3.16/A2
T24: JDIO.6, U$3.24
T25: JDIO.7, U$3.25
T26: JDIO.8, U$3.26
T27: JDIO.9, U$3.27
T28: JDIO.10, U$3.28
T29: JDIO.11, U$3.29
T30: JDIO.12, U$3.30
T32: JDIO.13, U$3.32/A13
TA14: JAIO.15, U$3.33/A14
TA15: JAIO.16, U$3.34/A15
TA16: JAIO.14, U$3.35/A16
TA17: JAIO.12, U$3.36/A17
TA18: JAIO.10, U$3.37/A18
TA19: JAIO.8, U$3.38/A19
TA20: JAIO.6, U$3.39/A20
TDAC0: JAIO.2, U$3.21/DAC0
TDAC1: JAIO.4, U$3.A22/DAC1
TFT_CS: JTFT.7, U$3.6
TFT_DC: JTFT.6, U$3.12/MISO
TFT_RST: JTFT.5, U$3.17/A3
VIN: JMIDI.4, JPWR.11, JPWR.12, JTFT.2, JTFT.8, U$3.VIN

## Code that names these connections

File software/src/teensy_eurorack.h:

//
// Created by Moolet on 09/03/2021.
//
#ifndef TEENSY_EURORACK_TEENSY_EURORACK_H
#define TEENSY_EURORACK_TEENSY_EURORACK_H

#include "teensy_eurorack_pins.h"

#define TFT_SCLK 13     // SCLK can also use pin 14
#define TFT_MOSI 11     // MOSI can also use pin 7
#define TFT_CS   6      // CS & DC can use pins 2, 6, 9, 10, 15, 20, 21, 22, 23
#define TFT_DC    2     //  but certain pairs must NOT be used: 2+10, 6+9, 20+23, 21+22
#define TFT_RST   -1    // RST can use any pin

#define DA_CLK 27
#define DA_MOSI 26
#define DA_MISO 39
#define DA_SYNC 38
#define AD7607_BUSY 3
#define AD7607_START_CONVERSION 5
#define AD7607_CHIP_SELECT 36
#define AD7607_RESET 35
#define AD7607_RANGE_SELECT 37
#define LRCLK_CPY 40

unsigned memfree(void) {
    extern unsigned long _ebss;
    extern unsigned long _sdata;
    extern unsigned long _estack;
    const unsigned DTCM_START = 0x20000000UL;
    unsigned dtcm = (unsigned)&_estack - DTCM_START;
    unsigned stackinuse = (unsigned) &_estack -  (unsigned) __builtin_frame_address(0);
    unsigned varsinuse = (unsigned)&_ebss - (unsigned)&_sdata;
    unsigned freemem = dtcm - (stackinuse + varsinuse);
    return freemem;
}

#endif //TEENSY_EURORACK_TEENSY_EURORACK_H

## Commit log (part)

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2020-03-15 gerbers for 1.8.1
2020-03-15 Rename BOM-breakout.md to BOM-breakout.MD
2020-03-15 changed C26 from 4.7uf to 4.7uF, reduce number of distinct parts
2020-03-15 moved files in docs/
2020-03-17 corrected: unconnected trace
2020-03-17 updated silkscreen text
2020-03-17 updated gerbers
2020-03-18 fixed paths to 3d components and footprints
2020-03-20 improve pick n place manual
2020-04-25 change to read midi data from serial3 instead
2020-04-27 added ibom interactive boms
2020-06-15 v1.9 initial schematic, cleanup
2020-06-15 work in progress
2020-06-15 footprints
2020-06-16 pcb w-i-p
2020-06-18 slowly
2020-06-19 pin headers improvements
2020-06-19 single board, rough placement, abt to chop into 2 boards
2020-06-19 placing imprvmts
2020-06-19 schematic improvements
2020-06-20 silkscreen
2020-06-20 silkscreen, corrections
2020-06-20 erc pass
2020-06-22 split into two boards
2020-06-22 mainboard passes drc
2020-06-22 routing improv
2020-06-23 breakout DRC'ed
2020-06-24 minor tweeks to breakout board
2020-06-24 cleanup traces
2020-06-24 silkscreen improvments, gerbers, drc'ed
2020-06-24 images/ readme
2020-06-25 fix merge error
2020-07-22 updated path to boards
2020-07-22 changed schematic from A3 to A4
2020-07-22 repositioned board to middle of page
2020-07-23 schematic A3 -> A4 page
2020-07-23 recenter pcb in page
2020-07-24 test jest-junit annotations action
2020-07-25 docs from latest artifact
2020-07-25 actions: remove annotation step
2020-07-25 connected DAC_SCK output (pin 19) to pin 31, corrected audio out 4 AGND net (was disconnected)
2020-07-25 corrected audio out 4 AGND (was disconnected)
2020-07-25 corrected version number on schematic
2020-07-25 microsd adapter
2020-07-26 corrected TDM rx / tx pins
2020-07-26 remove LRCLK, doesnt seemed to be used, connected LRCLKs to gnd on codec.
2020-07-26 update pcb
2020-07-27 added gerbers for 1.9.1 updates, added uSD extender
2020-07-27 cleanup
2020-07-27 move docs to hardware
2020-07-27 update docs
2020-07-27 add svg of front panel
2020-07-27 add 3d model for acjs-mv5, updated footprint
2020-07-27 updated acjs-mv5 footprints
2020-07-27 update mainboard images
2020-07-27 Revert "recenter pcb in page"
    This reverts commit 40a09dfd2033d5d90cab69f8a1165afd283f11e8.
2020-07-27 corrected edge on breakout board
2020-07-27 images
2020-08-09 correction: re-connect LRCLK to codec - as its required for TDM audio protocol
2020-08-09 pcboard: re-connect LRCLK to codec, move hole for sd-extender cable further away from teensy, and move usb B headers up to avoid collision with SD-extender
2020-08-09 silkscreen improvements
2020-08-09 update revision in schematic
2020-08-10 via sizes corrected
2020-08-10 gerbers updated with correct via size
2020-09-05 fix schematic errors and change breakout to 4 layer board
2020-09-16 updated schematic to latest
2020-09-20 updated breakout board images
2020-09-20 software reset
2020-09-20 01 - control voltate out basic working
2020-09-20 changed status to "in testing"
2020-09-20 basic example using two dacs
2020-11-06 schematic: correct ADC_MISO to MISO1 (pin 39) and DA_SYNC to SPI1 CS (pin 38)
2020-11-06 schematic: correct ADC_RANGE (pin 37)
2020-11-06 schematic: corrections and updates
2020-11-07 schematic, pcb changes for v2.0
2020-11-07 updated version to v2.0
2020-11-07 mainboard: removed loopback for SPI clock as no longer needed
2020-11-15 corrections to breakout pcb
2020-11-28 schematic: change dac bypass caps to polar, correct polarity
2020-11-29 pcb: update polatity of +-12v bypass caps
2020-11-30 schematic: adc to use same external voltage reference as dac
2020-11-30 pcb: update from schematic and route as 4 layer board
2020-11-30 pcb: increase diameter of some via from 0.2mm to 0.25mm for jlcpcb
2020-12-01 pcb: update min via size to .45/.25 mm, routed as 4 layer
2020-12-22 soldermask clearance set to 0.05mm and minimum soldermask bridge to 0.2mm as per jlcpcb
2021-01-09 MAJOR: Correct polarity of +-12V on breakout boardgit add teensy-eurorack-breakout.sch
2021-01-09 MAJOR: breakout PCB correction to polarity of +12V
2021-01-09 Minor pcb improvements: pins of DAC on same net should not bridge if posible as it looks unintentional solder bridge
2021-01-27 Breakout: changed from 4 layer to 2 layer; Mainboard: add serial daisy chain RX/TX to RX4/TX4
2021-01-27 update board images
2021-01-27 fuck facebook
2021-01-30 mainboard pcb: spaced tracks out
2021-01-30 mainboard pcb: minor cleanup
2021-02-13 st7735: change vcc,reset,backlight from 5v to 3v3
2021-02-13 v.2.0.3
2021-02-25 update BOM
2021-02-27 example: simple CV scope
2021-02-27 curve example
2021-02-28 example: audio in -> cv out
2021-03-01 remove ref to DrawingCanvas.h
2021-03-01 audioin -> cvout
2021-03-01 Tie LRCLK pin 20 to pin40 to sync DAC/ADC sampling w/ audio sampling
2021-03-01 Mainboard PCB: Tie LRCLK pin20 to pin40 to sync DAC/ADC sampling w/ audio sampling
2021-03-07 example: audio in -> cv out with 2 simple scopes
2021-03-08 cv input simple scope x 2
2021-03-09 add PIN definitions for TFT display
2021-03-13 refactor examples folder, add PIN definitions for TFT display
2021-03-15 examples
2021-04-03 FIXED: add 1k pull-up resistor to MIDI rx pin
2021-04-03 breakout-board: silkscreen: add Kicad OpenSourceHardware logo
2021-04-03 mainboard-board: silkscreen: add Kicad OpenSourceHardware logo
2021-04-03 update schematics
2021-04-03 updated gerbers to v2.1
2021-04-03 gh-pages initial commit
2021-04-03 Set theme jekyll-theme-cayman
2021-04-03 Set theme jekyll-theme-hacker
2021-04-05 software example updates
2021-05-08 input_output_spi
2021-05-08 examples etc
2021-05-13 start of cleanup...
2021-05-13 examples....
2021-05-13 cleanup...
2021-05-13 build software
2021-05-13 correction...
2021-05-13 PaulStoffregen/Audio.git
2021-05-13 PaulStoffregen/ST7735_t3
2021-05-13 ResponsiveAnalogRead
2021-05-13 arduino_midi_library
2021-05-14 individual builds
2021-05-14 rename workflows
2021-05-14 correction
2021-05-14 corrections
2021-05-15 do not build on commit of .md files
2021-05-15 adding readme for examples, wip
2021-05-15 readme
2021-05-15 turn up the volume
2021-05-15 restructure + add basic mp3
2021-05-15 remove unused variable
2021-05-15 update workflows
2021-05-16 levels example
2021-05-16 analyze all audio channels
2021-05-16 add display levels to build
2021-06-11 pitch example
2021-06-11 toggle antialiasing
2021-07-22 readme: just testing
2021-11-08 Update README.md
    https://forum.kicad.info/t/warning-avoid-all-links-to-kicad-pcb-org-use-kicad-org/31521
2022-11-09 trigger kicad github action...
